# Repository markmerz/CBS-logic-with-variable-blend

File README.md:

# CBS-logic-with-variable-blend

My attempt at SQ decoder with MC1312, MC1314 and MC1315 chips.

Beware, I assembled the board but it didn't work right. It's still hooked up to meters in my bench, waiting for an inspiration. You can use the zip file for ordering your own boards if you feeling lucky.

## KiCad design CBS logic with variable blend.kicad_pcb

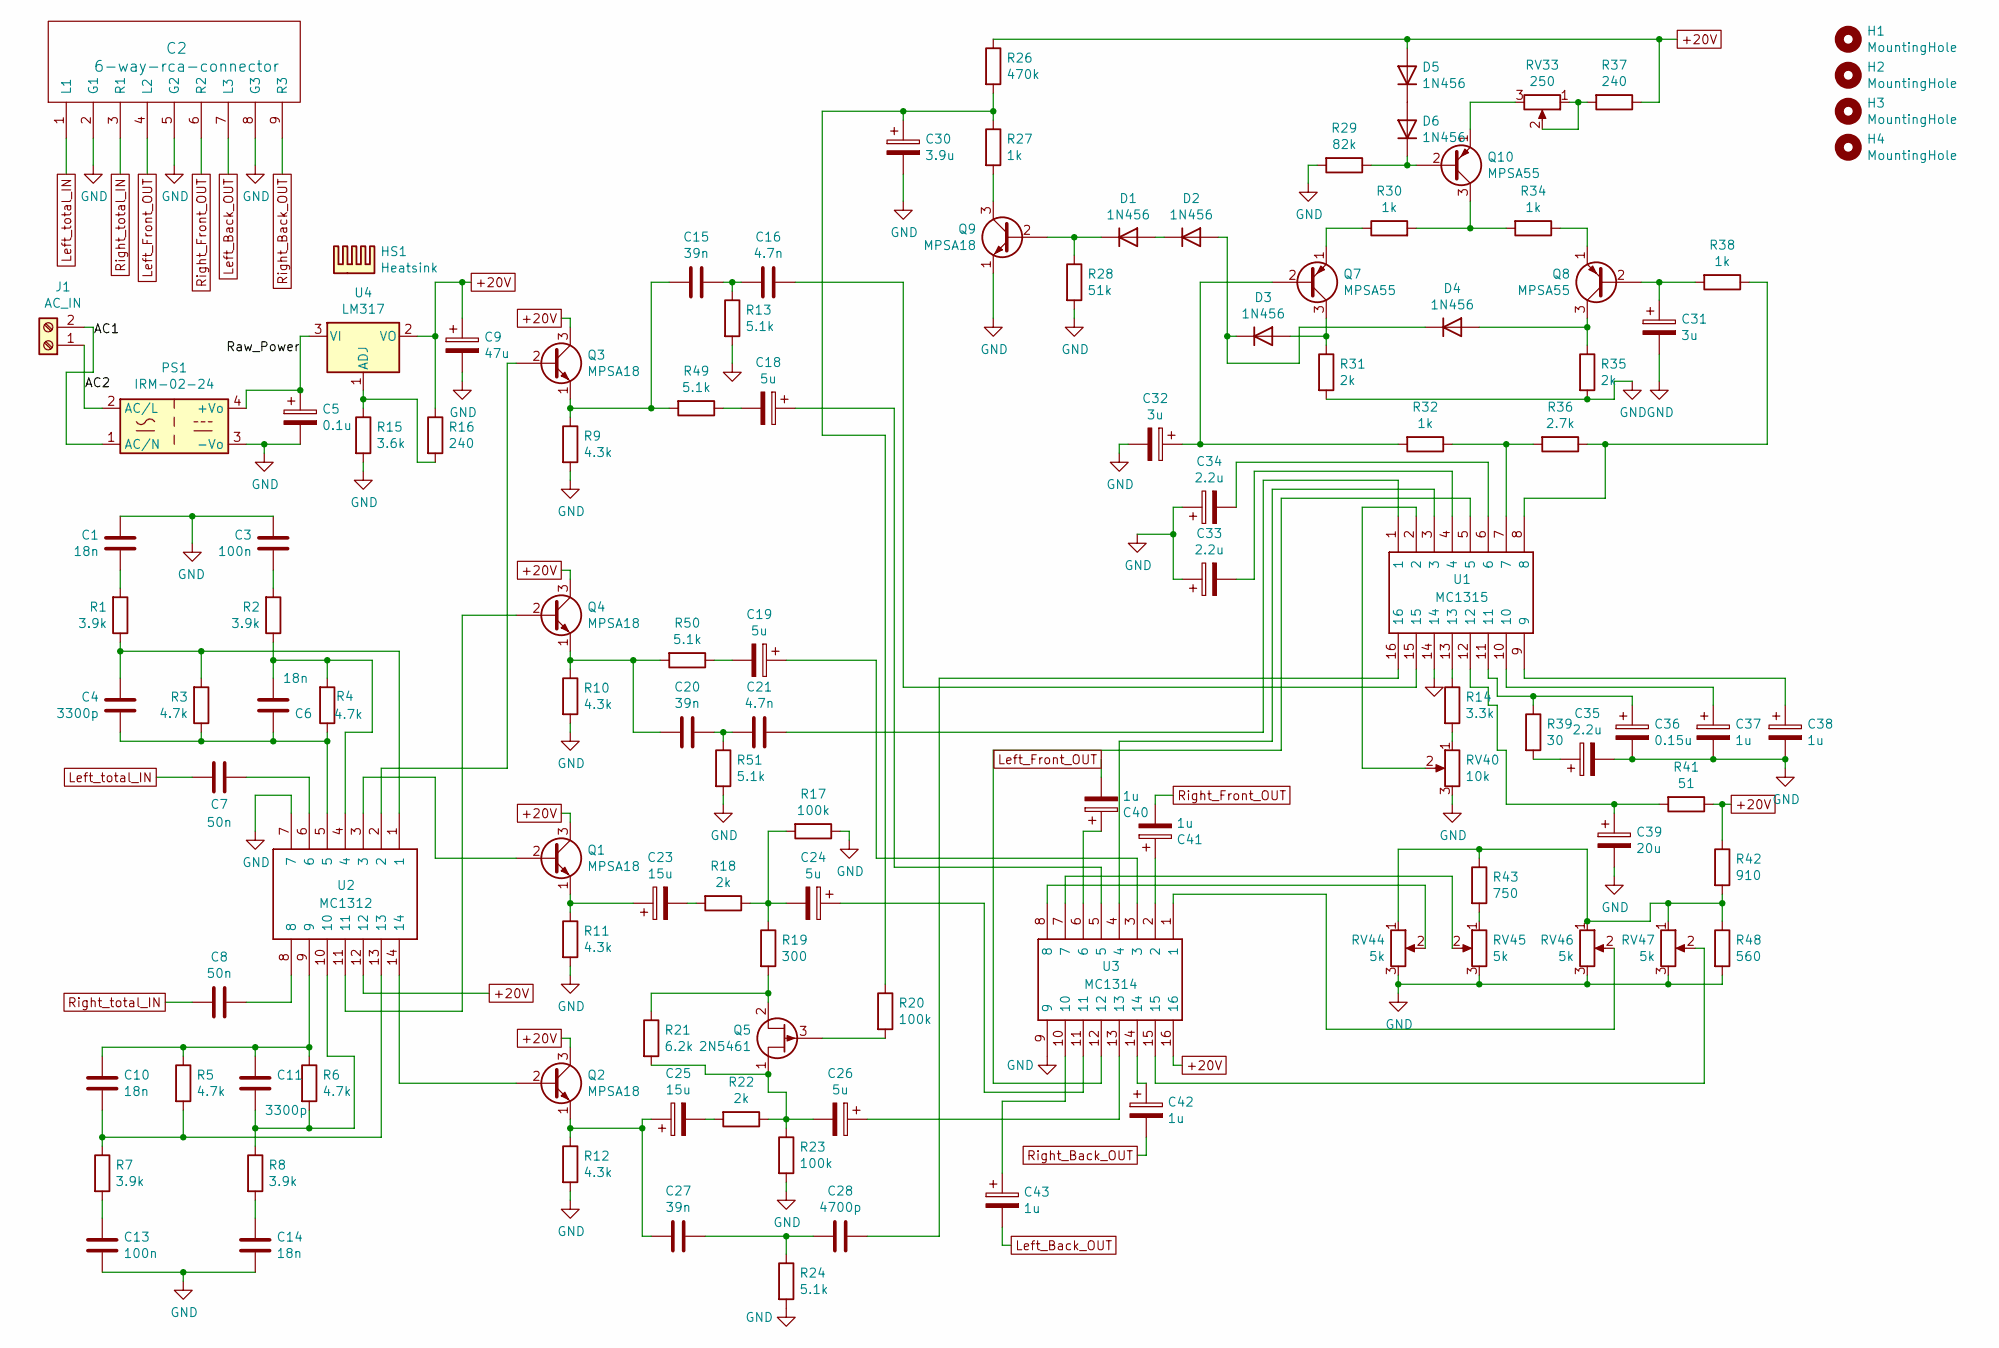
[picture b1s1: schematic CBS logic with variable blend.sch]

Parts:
C1, C6, C10, C14: 18n; C_Disc_D5.0mm_W2.5mm_P2.50mm
C2: 6-way-rca-connector; 6-way-rca-connector-on-edge
C3, C13: 100n; C_Disc_D5.0mm_W2.5mm_P2.50mm
C4, C11: 3300p; C_Disc_D5.0mm_W2.5mm_P2.50mm
C5: 0.1u; CP_Radial_D4.0mm_P2.00mm
C7, C8: 50n; C_Disc_D5.0mm_W2.5mm_P2.50mm
C9: 47u; CP_Radial_D4.0mm_P2.00mm
C15, C20, C27: 39n; C_Disc_D5.0mm_W2.5mm_P2.50mm
C16, C21: 4.7n; C_Disc_D5.0mm_W2.5mm_P2.50mm
C18, C19, C24, C26: 5u; CP_Radial_D4.0mm_P2.00mm
C23, C25: 15u; CP_Radial_D4.0mm_P2.00mm
C28: 4700p; C_Disc_D5.0mm_W2.5mm_P2.50mm
C30: 3.9u; CP_Radial_D4.0mm_P2.00mm
C31, C32: 3u; CP_Radial_D4.0mm_P2.00mm
C33, C34, C35: 2.2u; CP_Radial_D4.0mm_P2.00mm
C36: 0.15u; CP_Radial_D4.0mm_P2.00mm
C37, C38, C40, C41, C42, C43: 1u; CP_Radial_D4.0mm_P2.00mm
C39: 20u; CP_Radial_D4.0mm_P2.00mm
D1, D2, D3, D4, D5, D6: 1N456; D_DO-35_SOD27_P5.08mm_Vertical_KathodeUp
H1, H2, H3, H4: MountingHole; MountingHole_3.2mm_M3
HS1: Heatsink; to220_heatsink
J1: AC_IN; SCREWTERMINAL-5MM-2
PS1: IRM-02-24; Converter_ACDC_MeanWell_IRM-02-xx_THT
Q1, Q2, Q3, Q4, Q9: MPSA18; TO-92_Inline
Q5: 2N5461; TO-92_Inline
Q7, Q8, Q10: MPSA55; TO-92_Inline
R1, R2, R7, R8: 3.9k; R_Axial_DIN0207_L6.3mm_D2.5mm_P2.54mm_Vertical
R3, R4, R5, R6: 4.7k; R_Axial_DIN0207_L6.3mm_D2.5mm_P2.54mm_Vertical
R9, R10, R11, R12: 4.3k; R_Axial_DIN0207_L6.3mm_D2.5mm_P2.54mm_Vertical
R13, R24, R49, R50, R51: 5.1k; R_Axial_DIN0207_L6.3mm_D2.5mm_P2.54mm_Vertical
R14: 3.3k; R_Axial_DIN0207_L6.3mm_D2.5mm_P2.54mm_Vertical
R15: 3.6k; R_Axial_DIN0207_L6.3mm_D2.5mm_P2.54mm_Vertical
R16, R37: 240; R_Axial_DIN0207_L6.3mm_D2.5mm_P2.54mm_Vertical
R17, R20, R23: 100k; R_Axial_DIN0207_L6.3mm_D2.5mm_P2.54mm_Vertical
R18, R22, R31, R35: 2k; R_Axial_DIN0207_L6.3mm_D2.5mm_P2.54mm_Vertical
R19: 300; R_Axial_DIN0207_L6.3mm_D2.5mm_P2.54mm_Vertical
R21: 6.2k; R_Axial_DIN0207_L6.3mm_D2.5mm_P2.54mm_Vertical
R26: 470k; R_Axial_DIN0207_L6.3mm_D2.5mm_P2.54mm_Vertical
R27, R30, R32, R34, R38: 1k; R_Axial_DIN0207_L6.3mm_D2.5mm_P2.54mm_Vertical
R28: 51k; R_Axial_DIN0207_L6.3mm_D2.5mm_P2.54mm_Vertical
R29: 82k; R_Axial_DIN0207_L6.3mm_D2.5mm_P2.54mm_Vertical
R36: 2.7k; R_Axial_DIN0207_L6.3mm_D2.5mm_P2.54mm_Vertical
R39: 30; R_Axial_DIN0207_L6.3mm_D2.5mm_P2.54mm_Vertical
R41: 51; R_Axial_DIN0207_L6.3mm_D2.5mm_P2.54mm_Vertical
R42: 910; R_Axial_DIN0207_L6.3mm_D2.5mm_P2.54mm_Vertical
R43: 750; R_Axial_DIN0207_L6.3mm_D2.5mm_P2.54mm_Vertical
R48: 560; R_Axial_DIN0207_L6.3mm_D2.5mm_P2.54mm_Vertical
RV33: 250; Potentiometer_Bourns_3296W_Vertical
RV40: 10k; Potentiometer_Bourns_3296W_Vertical
RV44, RV45, RV46, RV47: 5k; Potentiometer_Bourns_3296W_Vertical
U1: MC1315; DIP-16_W7.62mm
U2: MC1312; DIP-14_W7.62mm
U3: MC1314; DIP-16_W7.62mm
U4: LM317; TO-220-3_Vertical

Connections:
+20V: C9.1, D5.2 (A), Q1.3 (C), Q2.3 (C), Q3.3 (C), Q4.3 (C), R16.1, R26.1, R37.1, R41.1, R42.1, U2.12, U3.16, U4.2 (VO)
/AC1: J1.2, PS1.1 (AC/N)
/AC2: J1.1, PS1.2 (AC/L)
/Raw_Power: C5.1, PS1.4 (+Vo), U4.3 (VI)
GND: C1.2, C2.2 (G1), C2.5 (G2), C2.8 (G3), C3.2, C5.2, C9.2, C13.2, C14.2, C30.2, C31.2, C32.2, C33.1, C34.1, C35.2, C36.2, C37.2, C38.2, C39.2, PS1.3 (-Vo), Q9.1 (E), R9.2, R10.2, R11.2, R12.2, R13.2, R15.2, R17.1, R23.2, R24.2, R28.2, R29.2, R31.2, R35.2, R48.2, R51.2, RV40.3, RV44.3, RV45.3, RV46.3, RV47.3, U1.14, U2.7, U3.9
Left_Back_OUT: C2.7 (L3), C43.2
Left_Front_OUT: C2.4 (L2), C40.2
Left_total_IN: C2.1 (L1), C7.2
unnamed: C1.1, R1.2
unnamed: C3.1, R2.2
unnamed: C4.1, C6.1, R3.1, R4.1, U2.5
unnamed: C4.2, R1.1, R3.2, U2.1
unnamed: C6.2, R2.1, R4.2, U2.4
unnamed: C7.1, U2.6
unnamed: C8.1, U2.8
unnamed: C10.1, C11.1, R5.1, R6.1, U2.9
unnamed: C10.2, R5.2, R7.1, U2.13
unnamed: C11.2, R6.2, R8.1, U2.10
unnamed: C13.1, R7.2
unnamed: C14.1, R8.2
unnamed: C15.1, C16.2, R13.1
unnamed: C15.2, Q3.1 (E), R9.1, R49.2
unnamed: C16.1, U1.15
unnamed: C18.1, U3.5
unnamed: C18.2, R49.1
unnamed: C19.1, U3.3
unnamed: C19.2, R50.1
unnamed: C20.1, Q4.1 (E), R10.1, R50.2
unnamed: C20.2, C21.2, R51.1
unnamed: C21.1, U1.1
unnamed: C23.1, Q1.1 (E), R11.1
unnamed: C23.2, R18.2
unnamed: C24.1, U3.11
unnamed: C24.2, R17.2, R18.1, R19.1
unnamed: C25.1, C27.2, Q2.1 (E), R12.1
unnamed: C25.2, R22.2
unnamed: C26.1, U3.13
unnamed: C26.2, Q5.1 (S), R21.2, R22.1, R23.1
unnamed: C27.1, C28.2, R24.1
unnamed: C28.1, U1.16
unnamed: C30.1, R20.1, R26.2, R27.1
unnamed: C31.1, Q8.2 (B), R38.2
unnamed: C32.1, Q7.2 (B), R32.2
unnamed: C33.2, U1.4
unnamed: C34.2, U1.6
unnamed: C35.1, R39.2
unnamed: C36.1, R39.1, U1.11
unnamed: C37.1, U1.10
unnamed: C38.1, U1.9
unnamed: C39.1, R41.2, U1.12
unnamed: C40.1, U3.6
unnamed: C41.1, U3.2
unnamed: C42.1, U3.14
unnamed: C43.1, U3.10
unnamed: D1.1 (K), Q9.2 (B), R28.1
unnamed: D1.2 (A), D2.1 (K)
unnamed: D2.2 (A), D3.1 (K), D4.1 (K)
unnamed: D3.2 (A), Q7.3 (C), R31.1
unnamed: D4.2 (A), Q8.3 (C), R35.1
unnamed: D5.1 (K), D6.2 (A)
unnamed: D6.1 (K), Q10.2 (B), R29.1
unnamed: Q1.2 (B), U2.3
unnamed: Q2.2 (B), U2.14
unnamed: Q3.2 (B), U2.2
unnamed: Q4.2 (B), U2.11
unnamed: Q5.2 (D), R19.2, R21.1
unnamed: Q5.3 (G), R20.2
unnamed: Q7.1 (E), R30.1
unnamed: Q8.1 (E), R34.1
unnamed: Q9.3 (C), R27.2
unnamed: Q10.1 (E), RV33.3
unnamed: Q10.3 (C), R30.2, R34.2
unnamed: R14.1, U1.13
unnamed: R14.2, RV40.1
unnamed: R15.1, R16.2, U4.1 (ADJ)
unnamed: R32.1, R36.2, U1.7
unnamed: R36.1, R38.1, U1.8
unnamed: R37.2, RV33.1, RV33.2
unnamed: R42.2, R43.1, R48.1, RV44.1, RV46.1, RV47.1
unnamed: R43.2, RV45.1
unnamed: RV40.2, U1.2
unnamed: RV44.2, U3.8
unnamed: RV45.2, U3.7
unnamed: RV46.2, U3.1
unnamed: RV47.2, U3.15
unnamed: U1.3, U3.4
unnamed: U1.5, U3.12
Right_Back_OUT: C2.9 (R3), C42.2
Right_Front_OUT: C2.6 (R2), C41.2
Right_total_IN: C2.3 (R1), C8.2

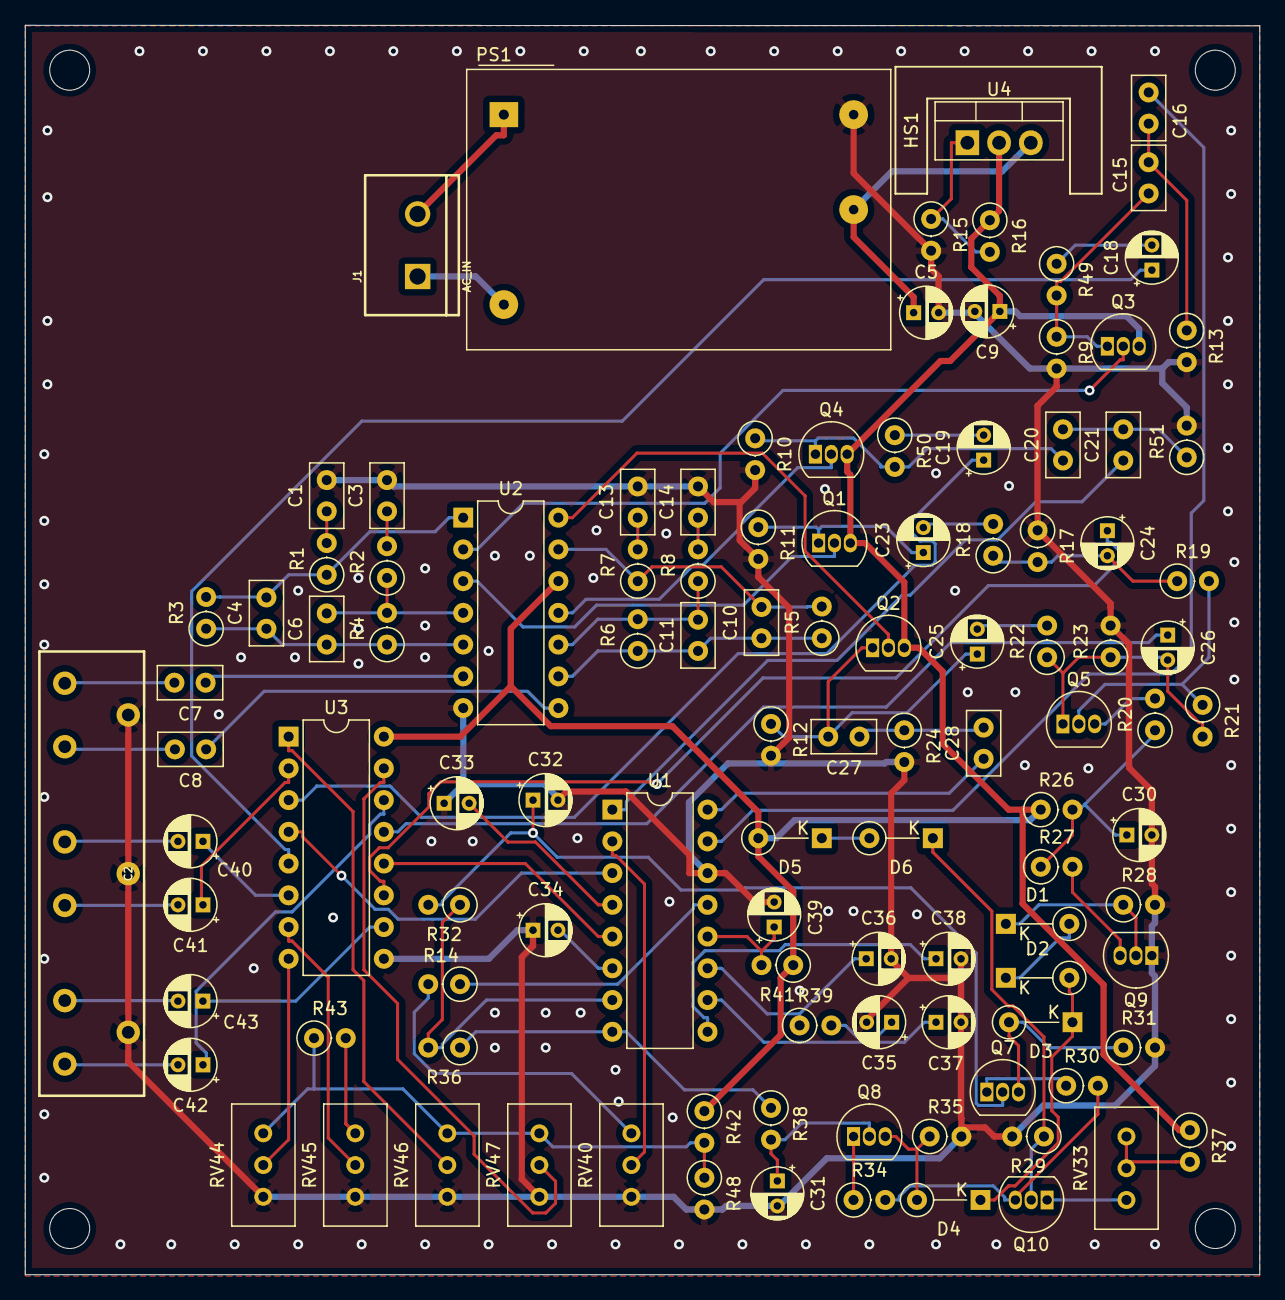
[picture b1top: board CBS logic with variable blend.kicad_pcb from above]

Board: 2 copper layers, 98.8 x 100.0 mm, 115 parts (0 on the bottom side), 90 nets.

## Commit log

2020-12-12 Minor corrections.
